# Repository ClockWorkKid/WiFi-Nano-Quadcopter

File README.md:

# Firefly
Micro quadcopter project (Under Development)

The objective of this project is to build an ultra low cost quadcopter platform for swarm of drones. (Inspired by <a href="https://espcopter.com/">ESP-Copter</a>, <a href="https://www.dronaaviation.com/product/">Pluto Drone</a>, <a href="https://www.ryzerobotics.com/tello">Ryze Tello</a>)

## Table of Contents

- [Build-1](#build-1)
- [TODO List](#todo-list)

## Build-1

The first build of the nano quad uses a 
- 90mm carbon fiber quadrotor frame
- 8520 coreless brushed motors
- 55mm propellers
- 600maH 1S Lipo cell
- WeMos D1 mini module as PPM receiver <a href="https://github.com/DipanshuShukla/ESP-PPM">(ESP-PPM)</a>
- SPRACING F3 EVO brushed flight controller

The reason behind using a ESP module instead of traditional RX modules is that ESP modules are easily programmable with the Arduino IDE, and ESP supports mesh networks which might be useful for swarming. The control interface is a web socket server that can be used from a smartphone browser with touch controls or firefox browser on PC with a traditional Gamepad. 

<figure align="center">
    
    <figcaption>Build 1</figcaption>
</figure>

Successful flight was achieved on September 2, 2020. For details on the build process, head on to the <a href="Build 1 - WiFi Quadcopter/README.md">Build-1 page</a>

## TODO List
- Port ESP8266 code to ESP32 (Build 1)
- Parameter Tuning (Build 1)
- Enable telemetry (Telemetry Test)
    - https://shipow.github.io/cleanflight-web/docs/telemetry.html
    - https://quadmeup.com/wifi-telemetry-for-cleanflight-with-ez-gui-and-esp8266/
    - https://diydrones.com/profiles/blogs/easy-to-use-frsky-library-for-arduino
    - https://github.com/sgofferj/arduino-frsky
    - https://ardupilot.org/copter/docs/common-frsky-telemetry.html
    - http://ceptimus.co.uk/?p=307
    - https://github.com/betaflight/betaflight/issues/6085
- Customizing Firmware
    - https://github.com/betaflight/betaflight/blob/master/docs/Customized%20Version.md
    - https://www.youtube.com/watch?v=37CP43OogQI
    - https://eecs.blog/compiling-betaflight-cleanflight-firmware-for-your-multirotor/
    - https://eecs.blog/adding-gps-back-to-cleanflight-for-f3-flight-controllers/
    - https://github.com/betaflight/betaflight/wiki/Betaflight-resource-remapping
    - https://www.reddit.com/r/Multicopter/comments/5rtcmn/adding_a_led_beeper_to_the_eachine_brushed_sp/
- Optical Flow Stabilization
    - https://robotzero.one/esp32-camera-module/
    - https://opencv-python-tutroals.readthedocs.io/en/latest/py_tutorials/py_video/py_lucas_kanade/py_lucas_kanade.html
    - https://robotics.stackexchange.com/questions/1844/stabilizing-a-quadcopter-with-optical-flow
- ESP Flight Controller 
    - https://github.com/rtlopez/esp-fc
    - https://github.com/PepeTheFroggie/EspCopter32
    - https://www.youtube.com/playlist?list=PLoPtpxJIxgnYnPrOeGHs3rdhhPgNGIYN5
- Other Tasks
    - https://dronerush.com/drone-gps-10778/
    - https://stackoverflow.com/questions/11217674/how-to-calculate-distance-from-wifi-router-using-signal-strength
    - https://www.kalmanfilter.net/background.html

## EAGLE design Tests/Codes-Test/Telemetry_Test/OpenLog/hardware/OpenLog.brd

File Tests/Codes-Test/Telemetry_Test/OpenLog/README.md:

SparkFun OpenLog
================

<table class="table table-hover table-striped table-bordered">
  <tr align="center">
   <td></td>
   <td></td>
  </tr>
  <tr align="center">
    <td><i>SparkFun OpenLog (<a href="https://www.sparkfun.com/products/13712">DEV-13712</a>)</i></td>
    <td><i>SparkFun OpenLog with Headers (<a href="https://www.sparkfun.com/products/13955">DEV-13955</a>)</i></td>
  </tr>
</table>

OpenLog is an open source data logger that works over a simple serial connection and supports microSD cards up to 64GB. 

Repository Contents
-------------------
* **/Documentation** - Data sheets, additional product information
* **/Firmware** - Example sketches for the OpenLog, and for an Arduino connected to the OpenLog.
* **/Hardware** - Hardware design files for the OpenLog PCB. These files were designed in Eagle CAD.
* **/Libraries** - Libraries for use with the OpenLog.
* **/Production** - Production panel files (.brd)

Documentation
--------------
* **[Hookup Guide](https://learn.sparkfun.com/tutorials/openlog-hookup-guide)** - Basic hookup guide for the OpenLog.
* **[SparkFun Fritzing repo](https://github.com/sparkfun/Fritzing_Parts)** - Fritzing diagrams for SparkFun products.
* **[SparkFun 3D Model repo](https://github.com/sparkfun/3D_Models)** - 3D models of SparkFun products. 
* **[SparkFun Graphical Datasheets](https://github.com/sparkfun/Graphical_Datasheets)** -Graphical Datasheets for various SparkFun products.

License Information
-------------------

This product is _**open source**_! 

Please review the LICENSE.md file for license information. 

If you have any questions or concerns on licensing, please contact techsupport@sparkfun.com.

Distributed as-is; no warranty is given.

- Your friends at SparkFun.

_SDFatLib-beta and SerialPort are written by Bill Greiman, and released under GPLv3._

Version History
---------------

For a full view of changes please see the [changelog](https://github.com/sparkfun/OpenLog/blob/master/CHANGELOG.md). 

OpenLog v4 is refactored with better RAM utilization for better performance at higher record speeds (115200/57600).

OpenLog v3 is stable, supports FAT32 cards up to 64GB and supports higher record speeds (115200/57600).

OpenLog v2 is a bit buggy but supports FAT32 and SD cards up to 16GB.  

OpenLog v1 is stable but only supports FAT16 and up to 2GB.  

* **v1.0**  Buggy initial release
* **v1.1**  Small changes to system settings and EEPROM storage.
* **v1.2**  Added wild card to listing and remove commands. Added read file command.
* **v1.3**  Added auto buffer record if unit sits idle for more than 5 seconds.
* **v1.4**  Increase buffer size to 900 bytes. Pinning down URU errors.
* **v1.5**  Lowered power consumption to ~2mA avg. Added 4800 and 19200 baud rates.
* **v1.51** Added configurable escape character, and escape character amount.
* **v1.6**  Added ability to configure via config.txt file.
* **v2.0**  Massive overhaul. Ported to sdfatlib. Now supports FAT16/FAT32/SD/SDHC.
* **v2.1**  Power save not working. Fixed issue 35. Dropping characters at 57600bps.
* **v2.11** Tested with 16GB microSD. Fixed issues 30 & 34. Re-enable power save.
* **v2.2**  Modified append_file() to use a single buffer. Increased HardwareSerial.cpp buffer to 512 bytes.
* **v2.21** ringp fork brought in. rm dir, cd .., and wildcards now work!
* **v2.3**  Migrated to v10.10.10 of sdfatlib. Moved to inline RX interrupt and buffer.
* **v2.4**  Merged ringp updates. Commands cd, rm, ls work again!
* **v2.41** Power loss bug fixed. Adding support for 38400bps for testing with SparkFum 9DOF IMU logging. 
* **v2.5**  Added software reset command. Modified the read command to print extended ASCII characters.
* **v2.51** Changed command prompt control to ignore \n for easier control from microcontroller.
* **v3.0**  Migration to Arduino v1.0 and better recording speed at 115200bps and 57600bps.
* **v3.1**  Better handling of recording during power loss.
* **v3.2**  Freed up RAM for larger RX ring buffer. Added support for wildcards and ability to ignore emergency override.
* **v3.3**  Added ability to ignore escape character checking and corrected incremental log naming.
* **v4.0**  Re-worked to be compatible with Arduino v1.6.x. Freed RAM to increase RX buffer size.

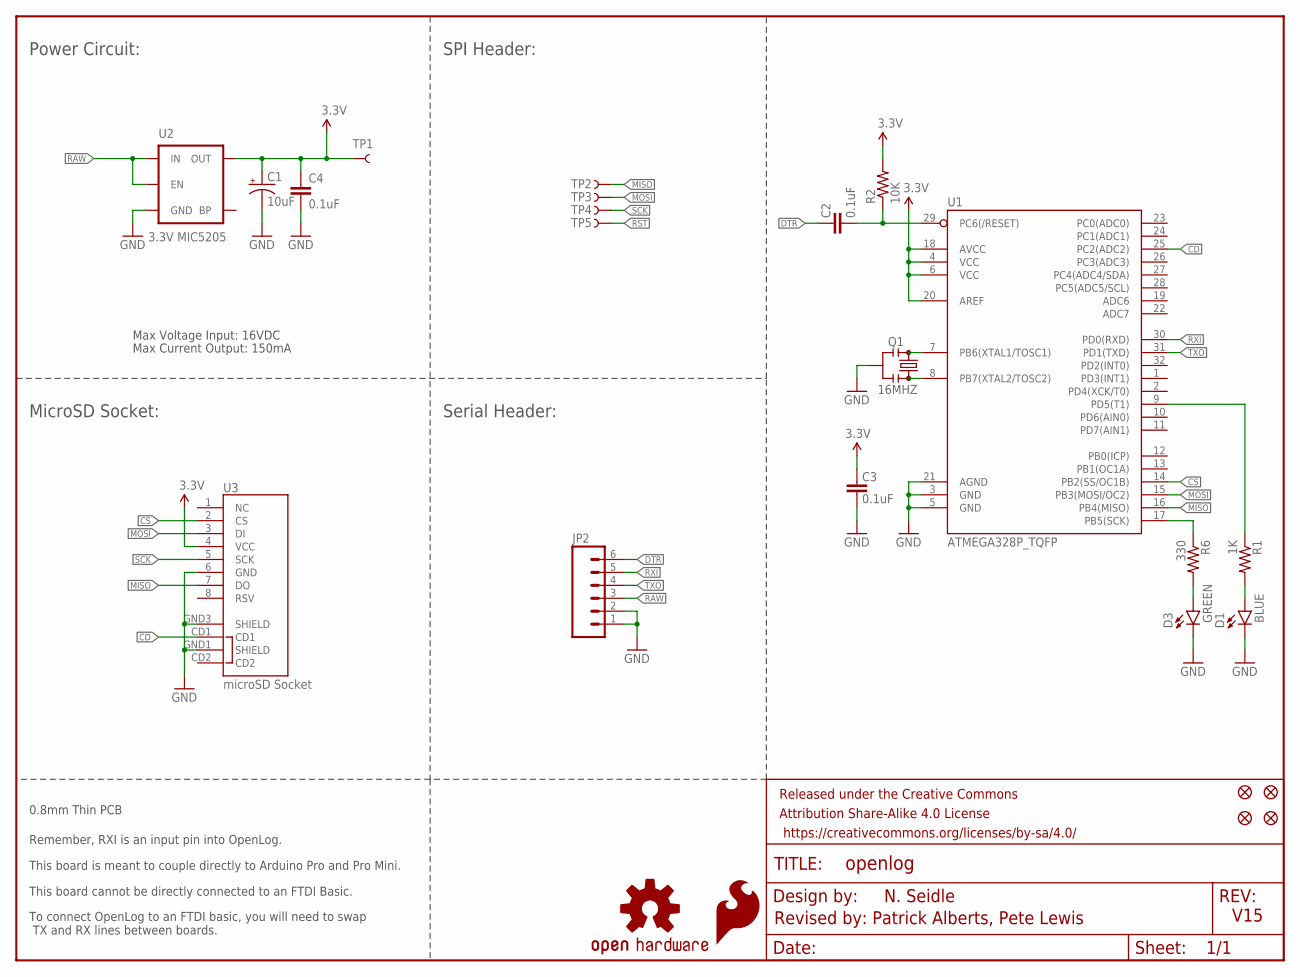
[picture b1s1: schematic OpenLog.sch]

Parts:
C1: 10uF; 0603-POL
C2, C3, C4: 0.1uF; 0603-CAP
D1: BLUE; LED-0603
D3: GREEN; LED-0603
FID1, FID2, FID3, FID4: FIDUCIALUFIDUCIAL; MICRO-FIDUCIAL
FRAME1: FRAME-LETTER; CREATIVE_COMMONS
JP2: M06NO_SILK_FEMALE_PTH; 1X06_NO_SILK
LOGO1: SFE_LOGO_FLAME.1_INCH; SFE_LOGO_FLAME_.1
LOGO2: OSHW-LOGOMINI; OSHW-LOGO-MINI
Q1: 16MHZ; RESONATOR-SMD
R1: 1K; 0603-RES
R2: 10K; 0603-RES
R6: 330; 0603-RES
TP1, TP2, TP3, TP4, TP5: TEST-POINT3; PAD.03X.03
U1: ATMEGA328P_TQFP; TQFP32-08
U2: 3.3V MIC5205; SOT23-5
U3: microSD Socket; MICROSD_1:1

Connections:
3.3V: C1.A (+), C3.2, C4.1, R2.2, TP1.P$1, U1.4 (VCC), U1.6 (VCC), U1.18 (AVCC), U1.20 (AREF), U2.5 (OUT), U3.4 (VCC)
CD: U1.25 (PC2(ADC2)), U3.CD1
CS: U1.14 (PB2(SS/OC1B)), U3.2 (CS)
DTR: C2.2, JP2.6
GND: C1.K (-), C3.1, C4.2, D1.C, D3.C, JP2.1, JP2.2, Q1.2, U1.3 (GND), U1.5 (GND), U1.21 (AGND), U2.2 (GND), U3.6 (GND), U3.GND1 (SHIELD), U3.GND3 (SHIELD)
MISO: TP2.P$1, U1.16 (PB4(MISO)), U3.7 (DO)
MOSI: TP3.P$1, U1.15 (PB3(MOSI/OC2)), U3.3 (DI)
unnamed: Q1.1, U1.8 (PB7(XTAL2/TOSC2))
unnamed: Q1.3, U1.7 (PB6(XTAL1/TOSC1))
unnamed: D1.A, R1.2
unnamed: R1.1, U1.9 (PD5(T1))
unnamed: D3.A, R6.2
RAW: JP2.3, U2.1 (IN), U2.3 (EN)
RST: C2.1, R2.1, TP5.P$1, U1.29 (PC6(/RESET))
RXI: JP2.5, U1.30 (PD0(RXD))
SCK: R6.1, TP4.P$1, U1.17 (PB5(SCK)), U3.5 (SCK)
TXO: JP2.4, U1.31 (PD1(TXD))

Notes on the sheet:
Max Voltage Input: 16VDC
Max Current Output: 150mA
Remember, RXI is an input pin into OpenLog.
This board is meant to couple directly to Arduino Pro and Pro Mini.
This board cannot be directly connected to an FTDI Basic.
To connect OpenLog to an FTDI basic, you will need to swap TX and RX lines between boards.
V15
N. Seidle
Revised by: Patrick Alberts, Pete Lewis
0.8mm Thin PCB
Power Circuit:
Serial Header:
MicroSD Socket:
SPI Header:

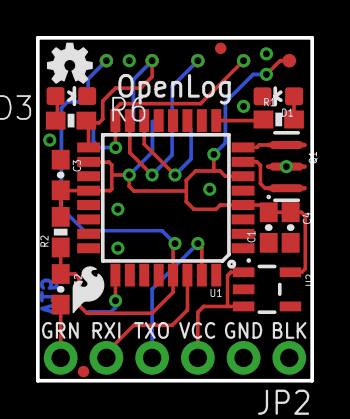
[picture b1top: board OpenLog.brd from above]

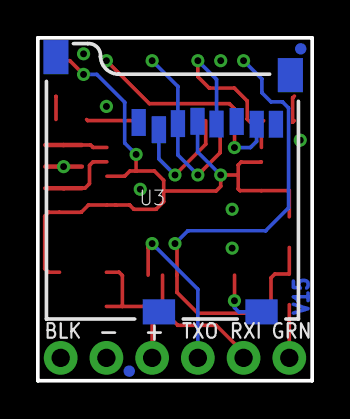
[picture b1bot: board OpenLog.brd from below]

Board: 2 copper layers, 15.2 x 19.1 mm, 26 parts (3 on the bottom side), 17 nets.

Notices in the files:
parts and their libraries:
SparkFun-Connectors: Licensing: Creative Commons ShareAlike 4.0 International - https://creativecommons.org/licenses/by-sa/4.0
SparkFun-Aesthetics: Released under the Creative Commons Attribution Share-Alike 4.0 License
SparkFun-Aesthetics: https://creativecommons.org/licenses/by-sa/4.0
